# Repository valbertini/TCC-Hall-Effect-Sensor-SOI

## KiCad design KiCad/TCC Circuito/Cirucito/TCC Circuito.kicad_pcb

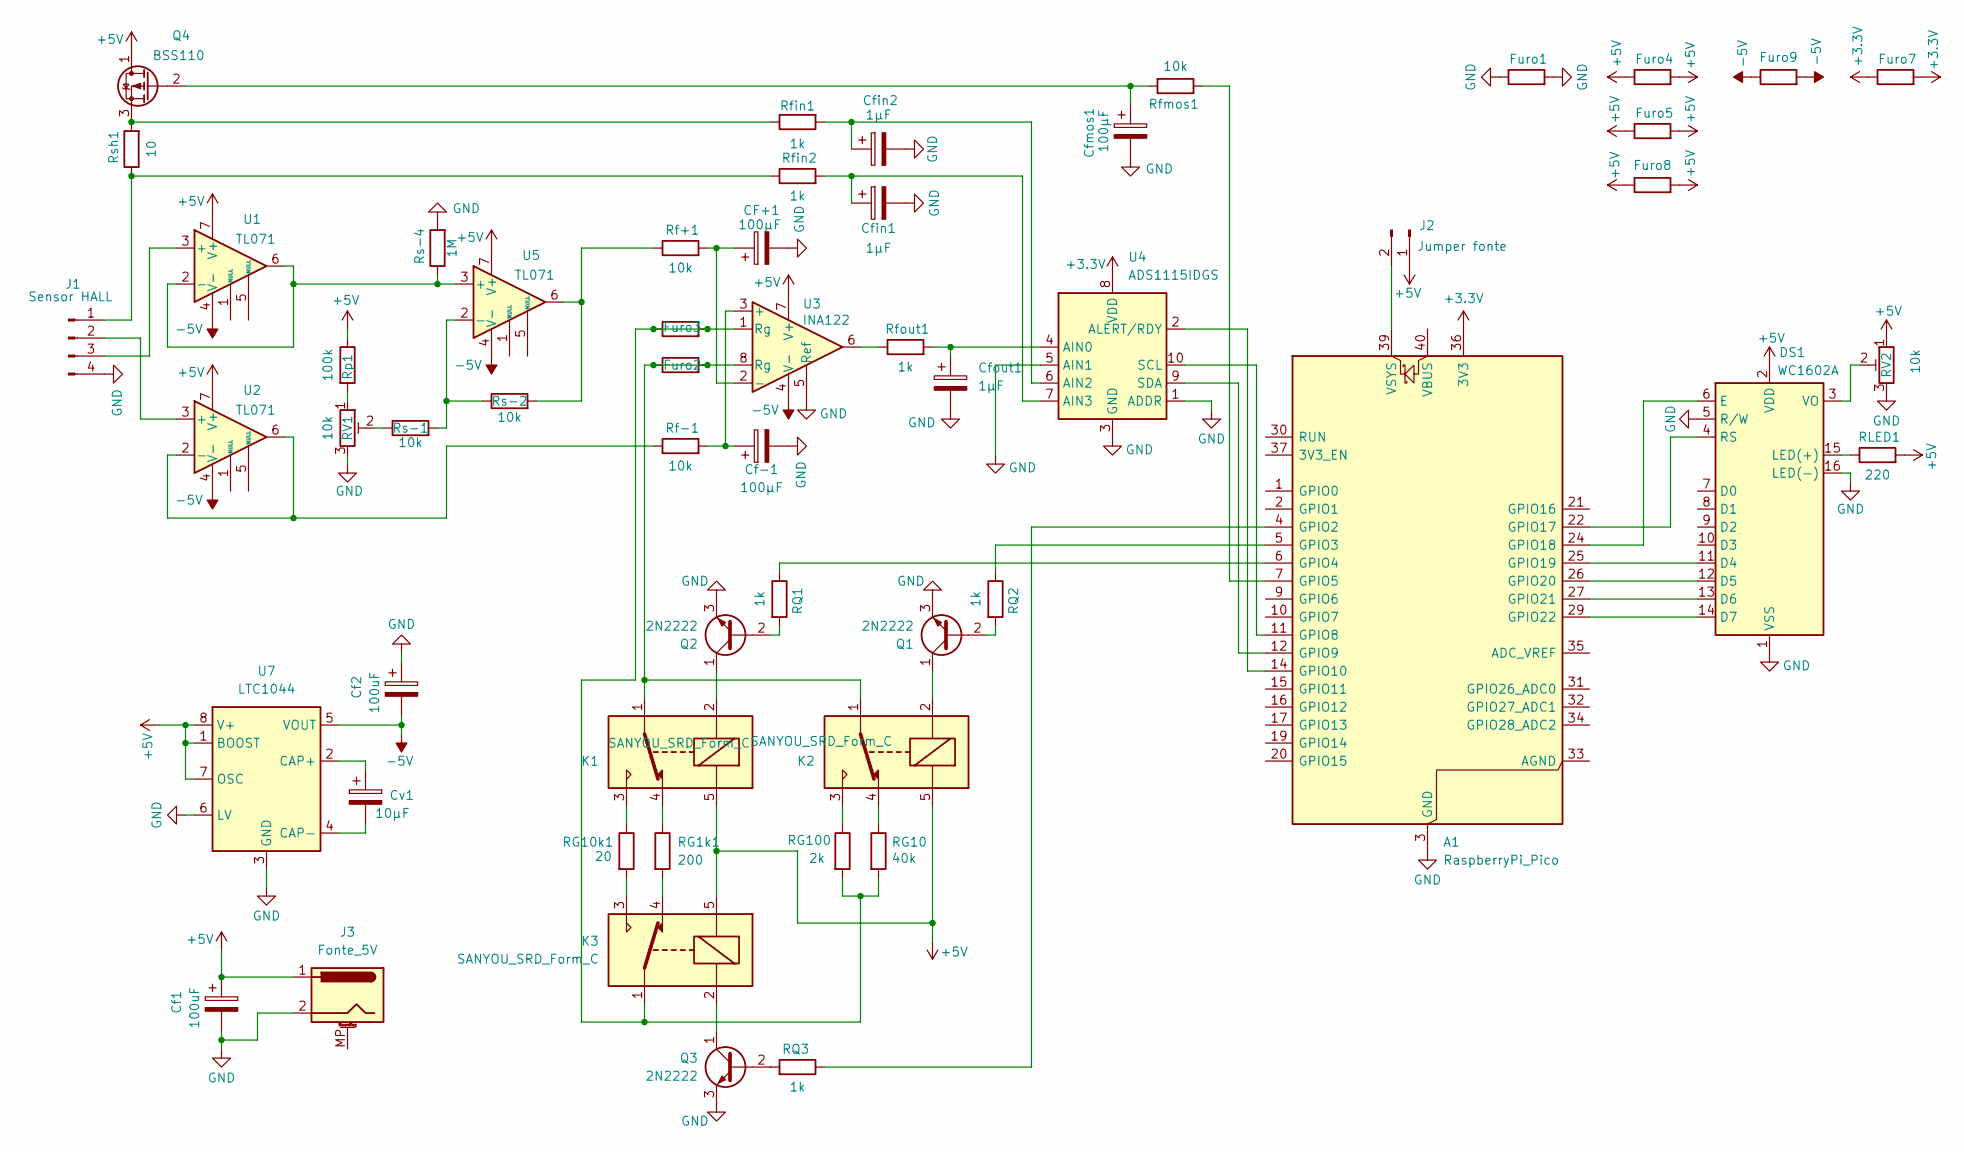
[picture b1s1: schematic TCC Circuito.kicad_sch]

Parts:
A1: RaspberryPi_Pico; RaspberryPi_Pico_Common_Unspecified
CF+1: 100μF; CP_Radial_D8.0mm_P3.50mm
Cf1, Cf2: 100uF; CP_Radial_D8.0mm_P3.50mm
Cf-1: 100μF; CP_Radial_D8.0mm_P3.50mm
Cfin1, Cfin2: 1μF; CP_Radial_D4.0mm_P2.00mm
Cfmos1: 100μF; CP_Radial_D8.0mm_P3.50mm
Cfout1: 1μF; CP_Radial_D4.0mm_P2.00mm
Cv1: 10μF; CP_Radial_D4.0mm_P2.00mm
DS1: WC1602A
Furo1: 0; R_Axial_DIN0207_L6.3mm_D2.5mm_P5.08mm_Vertical
Furo2, Furo3, Furo8: 0; R_Axial_DIN0207_L6.3mm_D2.5mm_P15.24mm_Horizontal
Furo4, Furo5, Furo9: 0; R_Axial_DIN0207_L6.3mm_D2.5mm_P10.16mm_Horizontal
Furo7: 0; R_Axial_DIN0309_L9.0mm_D3.2mm_P25.40mm_Horizontal
J1: Sensor HALL; PinHeader_1x04_P2.54mm_Vertical
J2: Jumper fonte; PinSocket_1x02_P2.54mm_Vertical
J3: Fonte_5V; BarrelJack_GCT_DCJ200-10-A_Horizontal
K1, K2, K3: SANYOU_SRD_Form_C; Relay_SPDT_SANYOU_SRD_Series_Form_C
Q1, Q2, Q3: 2N2222; TO-92_Inline_Wide
Q4: BSS110; TO-92_Inline_Wide
RG1k1: 200; R_Axial_DIN0207_L6.3mm_D2.5mm_P7.62mm_Horizontal
RG10: 40k; R_Axial_DIN0207_L6.3mm_D2.5mm_P7.62mm_Horizontal
RG10k1: 20; R_Axial_DIN0207_L6.3mm_D2.5mm_P7.62mm_Horizontal
RG100: 2k; R_Axial_DIN0207_L6.3mm_D2.5mm_P7.62mm_Horizontal
RLED1: 220; R_Axial_DIN0207_L6.3mm_D2.5mm_P10.16mm_Horizontal
RQ1, RQ2, RQ3: 1k; R_Axial_DIN0207_L6.3mm_D2.5mm_P7.62mm_Horizontal
RV1, RV2: 10k; Potentiometer_Bourns_3296W_Vertical
Rf+1: 10k; R_Axial_DIN0207_L6.3mm_D2.5mm_P7.62mm_Horizontal
Rf-1: 10k; R_Axial_DIN0207_L6.3mm_D2.5mm_P10.16mm_Horizontal
Rfin1, Rfin2: 1k; R_Axial_DIN0207_L6.3mm_D2.5mm_P10.16mm_Horizontal
Rfmos1: 10k; R_Axial_DIN0207_L6.3mm_D2.5mm_P7.62mm_Horizontal
Rfout1: 1k; R_Axial_DIN0207_L6.3mm_D2.5mm_P7.62mm_Horizontal
Rp1: 100k; R_Axial_DIN0207_L6.3mm_D2.5mm_P10.16mm_Horizontal
Rs-1, Rs-2: 10k; R_Axial_DIN0207_L6.3mm_D2.5mm_P10.16mm_Horizontal
Rs-4: 1M; R_Axial_DIN0207_L6.3mm_D2.5mm_P10.16mm_Horizontal
Rsh1: 10; R_Axial_DIN0207_L6.3mm_D2.5mm_P7.62mm_Horizontal
U1, U2, U5: TL071; DIP-8_W7.62mm_Socket
U3: INA122; DIP-8_W7.62mm_Socket
U4: ADS1115IDGS; PinHeader_1x10_P2.54mm_Vertical
U7: LTC1044; DIP-8_W7.62mm_Socket

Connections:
+3.3V: A1.36 (3V3), Furo7.1, Furo7.2, U4.8 (VDD)
+5V: Cf1.1, DS1.2 (VDD), Furo4.1, Furo4.2, Furo5.1, Furo5.2, Furo8.1, Furo8.2, J2.1, J3.1, K1.5, K2.5, K3.5, Q4.1 (D), RLED1.2, RV2.1, Rp1.1, U1.7 (V+), U2.7 (V+), U3.7 (V+), U5.7 (V+), U7.1 (BOOST), U7.7 (OSC), U7.8 (V+)
-5V: Cf2.2, Furo9.1, Furo9.2, U1.4 (V-), U2.4 (V-), U3.4 (V-), U5.4 (V-), U7.5 (VOUT)
GND: A1.3 (GND), A1.8 (GND), A1.13 (GND), A1.18 (GND), A1.23 (GND), A1.28 (GND), A1.38 (GND), CF+1.2, Cf1.2, Cf2.1, Cf-1.2, Cfin1.2, Cfin2.2, Cfmos1.2, Cfout1.2, DS1.1 (VSS), DS1.5 (R/W), DS1.16 (LED(-)), Furo1.1, Furo1.2, J1.4, J3.2, Q1.3 (E), Q2.3 (E), Q3.3 (E), RV1.3, RV2.3, Rs-4.2, U3.5 (Ref), U4.1 (ADDR), U4.3 (GND), U4.5 (AIN1), U7.3 (GND), U7.6 (LV)
unnamed: A1.4 (GPIO2), RQ3.1
unnamed: A1.5 (GPIO3), RQ2.1
unnamed: A1.6 (GPIO4), RQ1.1
unnamed: A1.7 (GPIO5), Rfmos1.1
unnamed: A1.11 (GPIO8), U4.10 (SCL)
unnamed: A1.12 (GPIO9), U4.9 (SDA)
unnamed: A1.14 (GPIO10), U4.2 (ALERT/RDY)
unnamed: A1.22 (GPIO17), DS1.4 (RS)
unnamed: A1.24 (GPIO18), DS1.6 (E)
unnamed: A1.25 (GPIO19), DS1.11 (D4)
unnamed: A1.26 (GPIO20), DS1.12 (D5)
unnamed: A1.27 (GPIO21), DS1.13 (D6)
unnamed: A1.29 (GPIO22), DS1.14 (D7)
unnamed: A1.39 (VSYS), J2.2
unnamed: DS1.15 (LED(+)), RLED1.1
unnamed: DS1.3 (VO), RV2.2
unnamed: Furo2.1, Furo2.2, K1.1, K2.1, U3.8 (Rg)
unnamed: Furo3.1, Furo3.2, K3.1, RG10.2, RG100.2, U3.1 (Rg)
unnamed: J1.1, Rfin2.1, Rsh1.1
unnamed: J1.2, U2.3 (+)
unnamed: J1.3, U1.3 (+)
unnamed: K1.3, RG10k1.1
unnamed: K1.4, RG1k1.1
unnamed: K2.3, RG100.1
unnamed: K2.4, RG10.1
unnamed: K3.3, RG10k1.2
unnamed: K3.4, RG1k1.2
unnamed: Q1.2 (B), RQ2.2
unnamed: K2.2, Q1.1 (C)
unnamed: Q2.2 (B), RQ1.2
unnamed: K1.2, Q2.1 (C)
unnamed: Q3.2 (B), RQ3.2
unnamed: K3.2, Q3.1 (C)
unnamed: Cfmos1.1, Q4.2 (G), Rfmos1.2
unnamed: Q4.3 (S), Rfin1.1, Rsh1.2
unnamed: RV1.1, Rp1.2
unnamed: RV1.2, Rs-1.1
unnamed: Rf+1.1, Rs-2.2, U5.6
unnamed: Rfout1.1, U3.6
unnamed: Rs-4.1, U1.2 (-), U1.6, U5.3 (+)
unnamed: Rf-1.1, U2.2 (-), U2.6
unnamed: Cf-1.1, Rf-1.2, U3.3 (+)
unnamed: CF+1.1, Rf+1.2, U3.2 (-)
unnamed: Cfout1.1, Rfout1.2, U4.4 (AIN0)
unnamed: Cfin2.1, Rfin1.2, U4.6 (AIN2)
unnamed: Cfin1.1, Rfin2.2, U4.7 (AIN3)
unnamed: Rs-1.2, Rs-2.1, U5.2 (-)
unnamed: Cv1.1, U7.2 (CAP+)
unnamed: Cv1.2, U7.4 (CAP-)

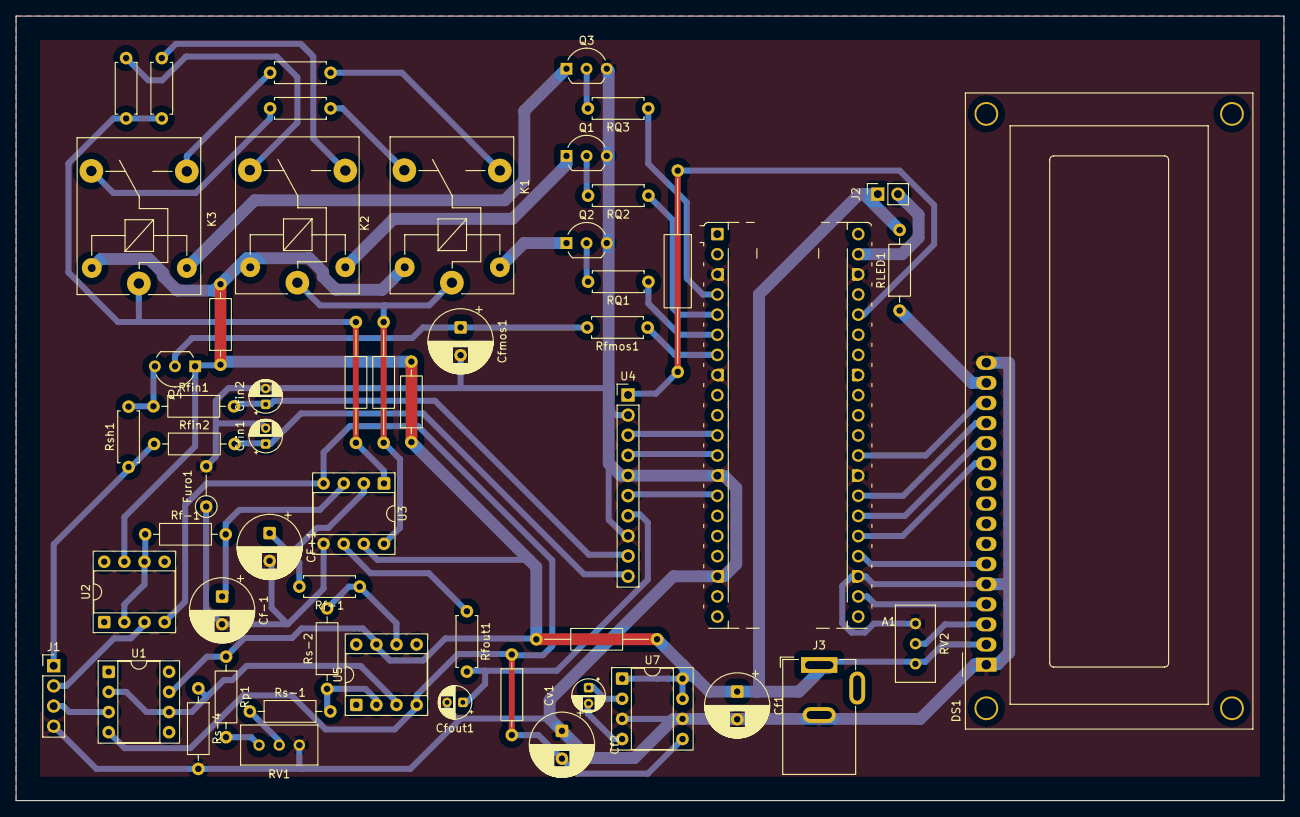
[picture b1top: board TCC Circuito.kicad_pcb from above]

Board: 2 copper layers, 160.0 x 99.0 mm, 56 parts (0 on the bottom side), 53 nets.

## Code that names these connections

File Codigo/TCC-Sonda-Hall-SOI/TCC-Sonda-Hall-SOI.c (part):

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 *  - Display LCD 16x2
 *
 * CONEXÕES:
 *  ADS1115 : SDA=GPIO9  SCL=GPIO8  ADDR=GND(0x48)
 *  Display  : RS=GPIO17 E=GPIO18 D4=GPIO19 D5=GPIO20 D6=GPIO21 D7=GPIO22
 *  Relés    : K1=GPIO2  K2=GPIO3  K3=GPIO4
 * ============================================================
 */

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
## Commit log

2025-12-08 Circuito inicial
2025-12-09 dois buffers
2025-12-11 ina122 e reles
2025-12-17 codigo ADC teste
2025-12-17 correções adc
2025-12-17 correc
2025-12-17 certo
2025-12-17 coorrc
2025-12-17 codigo com ADC funcionando bem
2025-12-17 kicad com filtros
2026-05-22 circuito final
2026-06-01 codigo e dados parciais
2026-06-01 dados completos
2026-06-01 kicad
